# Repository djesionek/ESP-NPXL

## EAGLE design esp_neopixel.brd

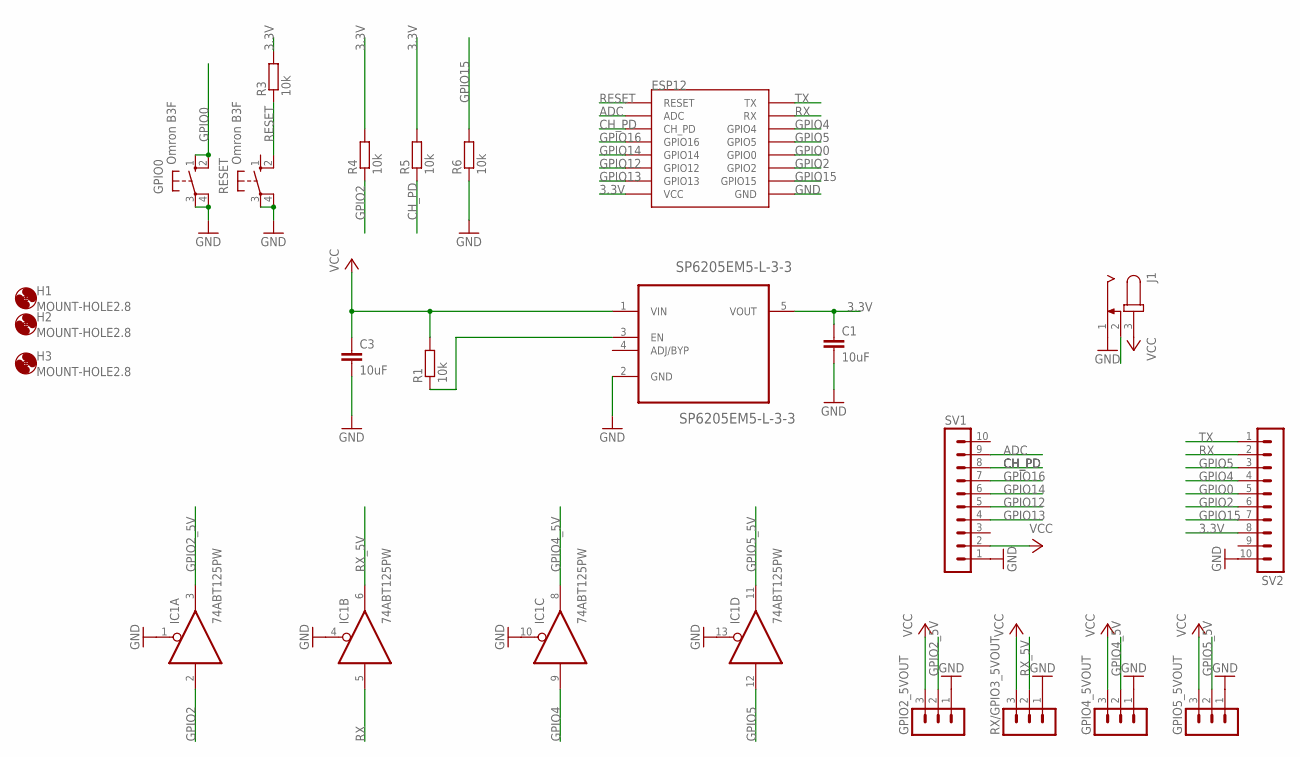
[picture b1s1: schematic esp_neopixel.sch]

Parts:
C1, C3: 10uF; C0805K
ESP12: ESP12
GPIO0: Omron B3F; B3F-10XX
GPIO2_5VOUT, GPIO4_5VOUT, GPIO5_5VOUT: MA03-1
H1, H2, H3: MOUNT-HOLE2.8; 2,8
IC1: 74ABT125PW; TSSOP14
J1: JACK-PLUG1; SPC4078
R1, R3, R4, R5, R6: 10k; M0805
RESET: Omron B3F; B3F-10XX
RX/GPIO3_5VOUT: MA03-1
SP6205EM5-L-3-3: SP6205EM5-L-3-3; SOT95P280X145-5N
SV1, SV2: MA10-1W

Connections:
3.3V: C1.1, ESP12.VCC, R3.2, R4.2, R5.2, SP6205EM5-L-3-3.5 (VOUT), SV2.8
ADC: ESP12.ADC, SV1.9
CH_PD: ESP12.CH_PD, R5.1, SV1.8
GND: C1.2, C3.2, ESP12.GND, GPIO0.3, GPIO0.4 (P1), GPIO2_5VOUT.1, GPIO4_5VOUT.1, GPIO5_5VOUT.1, IC1.1 (OE), IC1.4 (OE), IC1.7 (GND), IC1.10 (OE), IC1.13 (OE), J1.1, R6.1, RESET.3, RESET.4 (P1), RX/GPIO3_5VOUT.1, SP6205EM5-L-3-3.2 (GND), SV1.1, SV2.10
GPIO0: ESP12.GPIO0, GPIO0.1 (S), GPIO0.2 (S1), SV2.5
GPIO2: ESP12.GPIO2, IC1.2 (I), R4.1, SV2.6
GPIO2_5V: GPIO2_5VOUT.2, IC1.3 (O)
GPIO4: ESP12.GPIO4, IC1.9 (I), SV2.4
GPIO4_5V: GPIO4_5VOUT.2, IC1.8 (O)
GPIO5: ESP12.GPIO5, IC1.12 (I), SV2.3
GPIO5_5V: GPIO5_5VOUT.2, IC1.11 (O)
GPIO12: ESP12.GPIO12, SV1.5
GPIO13: ESP12.GPIO13, SV1.4
GPIO14: ESP12.GPIO14, SV1.6
GPIO15: ESP12.GPIO15, R6.2, SV2.7
GPIO16: ESP12.GPIO16, SV1.7
unnamed: R1.1, SP6205EM5-L-3-3.3 (EN)
RESET: ESP12.RESET, R3.1, RESET.2 (S1)
RX: ESP12.RX, IC1.5 (I), SV2.2
RX_5V: IC1.6 (O), RX/GPIO3_5VOUT.2
TX: ESP12.TX, SV2.1
VCC: C3.1, GPIO2_5VOUT.3, GPIO4_5VOUT.3, GPIO5_5VOUT.3, IC1.14 (VCC), J1.3, R1.2, RX/GPIO3_5VOUT.3, SP6205EM5-L-3-3.1 (VIN), SV1.2

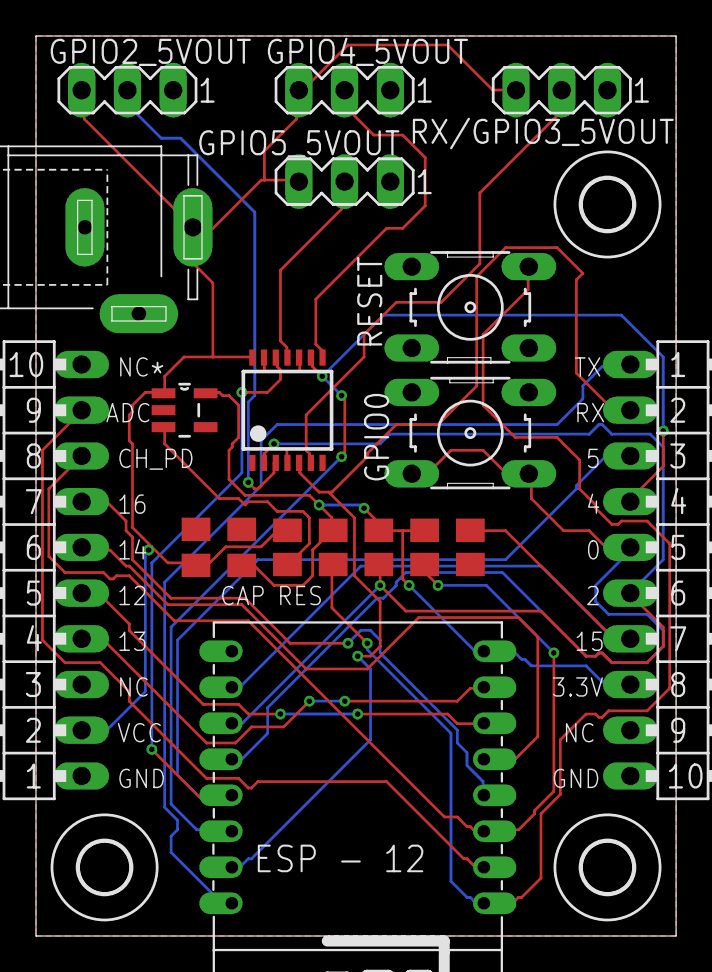
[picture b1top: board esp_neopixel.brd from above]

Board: 2 copper layers, 35.6 x 50.0 mm, 22 parts (0 on the bottom side), 22 nets.

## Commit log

2018-03-08 Moved project to git
2018-03-08 Fixed typo RADME.md -> README.md
